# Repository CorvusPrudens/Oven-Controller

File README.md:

# Oven-Controller
 Hardware Firmware, and support software for an ATMEGA 328-P based reflow oven controller.

## Hardware

 The board is controlled by an ATMEGA328-P microcontroller running at 20 MHz. USB communication and flashing is handled with an FT232R USB to UART IC. The board uses a USB-C connector because every modern device should.
 <!--  -->

 The controller includes a MAX31865 PTD temperature sensor IC with headers for a three-wire PTD probe, a solid state relay, and two additional gpio. The board also include a 7-12 volt power input header and a standard Arduino ICSP header for bootloader flashing.

 The most prominent feature is, of course, the 128x64 pixel OLED display. The on-screen UI is navigated with the 6 pushbuttons arranged in a gamepad-like fashion.

 The board was designed in kiCad, but can be easily ported to Eagle.
<br /><br />
## Firmware

 The firmware provides an intuitive, menu-based UI for the user. Without any programming or reflashing, the user can define up to eight temperature profiles that persist even after power cycling. These profiles can then be called up to control a modified toaster oven via a solid state relay.

 The firmware provides out of the box support for a piezo buzzer on the available gpio terminal, which provides feedback for UI navigation and an open-door notification.
<br /><br /><br /><br /><br /><br /><br /><br /><br /><br />
## Software
 I have also written a few support programs with Processing and Python. They perform various functions, including generating timer settings for different clock frequencies, generating playable note sequences given a semi-intuitive note table entry, generating bitmaps from images (ideally monochromatic or dichromatic images), and a program that allows a connected computer to log and display the live temperature profile as recorded by the controller.

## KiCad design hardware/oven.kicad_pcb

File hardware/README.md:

# Hardware

<!--  -->

 This board combines several convenient features together to make an easy to use and highly capable reflow (toaster) oven controller. At the heart of the design is an ATMEGA328-P, with a few support features similar to what you might find on an Arduino board. This allows easy integration with the large Arduino ecosystem and convenient communication and flashing via USB (after flashing a bootloader via the ICSP header). To maximize performance, the 328-P is run at 5 volts -- supplied by either the USB Vbus or the included 7-12 volts LDO regulator. This allows the microcontroller to run at its highest rated frequency, 20 MHz, which is just enough to run all the UI screens at 30 frames per second.

 While the microcontroller can accept 5 volts, the two SPI connected modules -- the MAX31865 PTD probe sensor IC and the OLED display -- need 3.3 volts. Their power is supplied through another LDO, and the communication is routed through a very convenient level shifter, the TXB0108.

 The board itself is a 4 layer design. Of course, 4 layers is completely overkill for this design and would make no sense for a high-volume product. However, this is _not_ a high-volume product, and the manufacturer I use just so happened to drop their 4 layer prices insanely low. I'd be crazy not to make it 4!

 Finally, I'd like to highlight the use of USB-C. If I ever include USB functionality on a device, I will _always_ choose USB-C if I am able. Not only is it an aesthetically pleasing, reversible, fast, and powerful connection -- it's _dead easy_ to design with assuming you don't need its fancier features like power delivery or USB 3.0 (or the dreadfully named USB 3.1 gen 2!). All that's needed for a basic implementation is two resistors and a convenient USB 2.0 rated connector like the one I've used on this board. Give it a try!

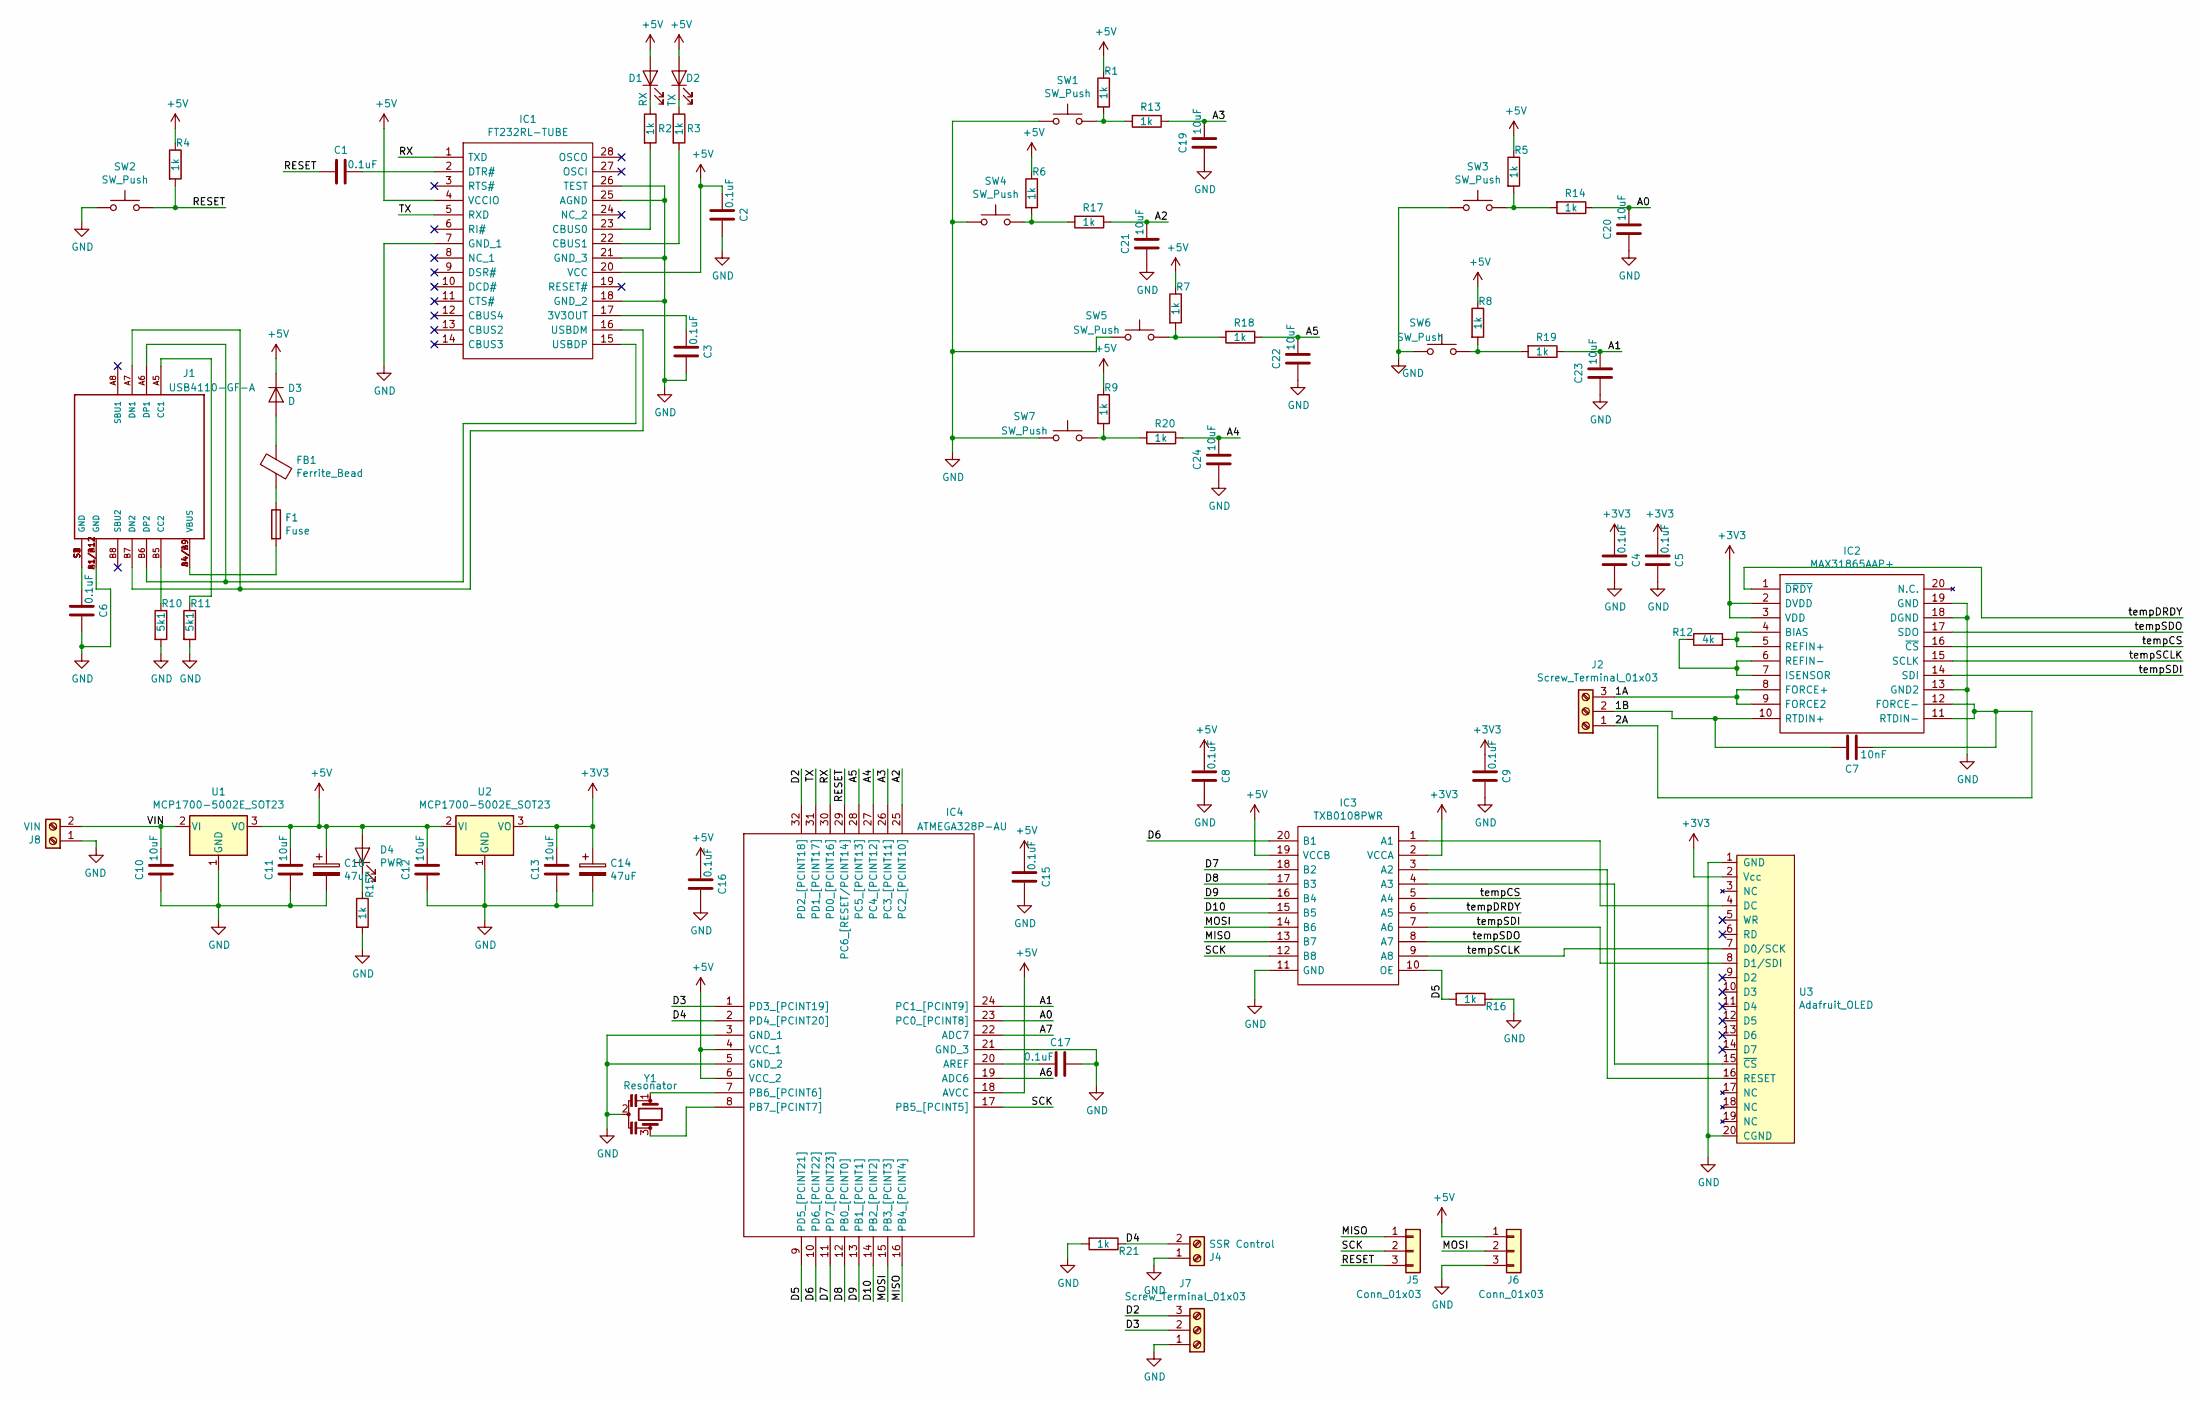
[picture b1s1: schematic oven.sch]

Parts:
C1, C2, C3, C4, C5, C6, C8, C9, C15, C16, C17: 0.1uF; C_0603_1608Metric_Pad1.05x0.95mm_HandSolder
C7: 10nF; C_0603_1608Metric_Pad1.05x0.95mm_HandSolder
C10, C11, C12, C13, C19, C20, C21, C22, C23, C24: 10uF; C_0805_2012Metric
C14, C18: 47uF; CP_EIA-3216-12_Kemet-S_Pad1.58x1.35mm_HandSolder
D1: RX; LED_0603_1608Metric_Pad1.05x0.95mm_HandSolder
D2: TX; LED_0603_1608Metric_Pad1.05x0.95mm_HandSolder
D3: D; DO-220AA
D4: PWR; LED_0603_1608Metric_Pad1.05x0.95mm_HandSolder
F1: Fuse; Fuse_0603_1608Metric_Pad1.05x0.95mm_HandSolder
FB1: Ferrite_Bead; L_0603_1608Metric_Pad1.05x0.95mm_HandSolder
IC1: FT232RL-TUBE; SOP65P780X200-28N; Mouser Part Number 895-FT232RL-TUBE
IC2: MAX31865AAP+; SOP65P778X199-20N; Mouser Part Number 700-MAX31865AAP+
IC3: TXB0108PWR; SOP65P640X120-20N; Mouser Part Number 595-TXB0108PWR
IC4: ATMEGA328P-AU; QFP80P900X900X120-32N; Mouser Part Number 556-ATMEGA328P-AU
J1: USB4110-GF-A; GCT_USB4110-GF-A
J2, J7: Screw_Terminal_01x03; TerminalBlock_4Ucon_1x03_P3.50mm_Horizontal
J4: SSR Control; TerminalBlock_4Ucon_1x02_P3.50mm_Horizontal
J5, J6: Conn_01x03; PinHeader_1x03_P2.54mm_Vertical
J8: VIN; TerminalBlock_4Ucon_1x02_P3.50mm_Horizontal
R1, R2, R3, R4, R5, R6, R7, R8, R9, R13, R14, R15, R16, R17, R18, R19, R20, R21: 1k; R_0603_1608Metric_Pad1.05x0.95mm_HandSolder
R10, R11: 5k1; R_0603_1608Metric_Pad1.05x0.95mm_HandSolder
R12: 4k; R_0603_1608Metric_Pad1.05x0.95mm_HandSolder
SW1, SW2, SW3, SW4, SW5, SW6, SW7: SW_Push; SW_PUSH_6mm_H4.3mm
U1, U2: MCP1700-5002E_SOT23; SOT-89-3
U3: Adafruit_OLED
Y1: Resonator; CSTNE16M0V530000R0

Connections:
+3V3: C4.2, C5.2, C9.2, C13.1, C14.1, IC2.2 (DVDD), IC2.3 (VDD), IC3.2 (VCCA), U2.3 (VO), U3.2 (Vcc)
+5V: C2.2, C8.2, C11.1, C12.1, C15.2, C16.2, C18.1, D1.2 (A), D2.2 (A), D3.1 (K), D4.2 (A), IC1.4 (VCCIO), IC1.20 (VCC), IC3.19 (VCCB), IC4.4 (VCC_1), IC4.6 (VCC_2), IC4.18 (AVCC), J6.1, R1.1, R4.1, R5.1, R6.1, R7.1, R8.1, R9.1, U1.3 (VO), U2.2 (VI)
/1A: IC2.8 (FORCE+), IC2.9 (FORCE2), J2.3
/1B: C7.1, IC2.10 (RTDIN+), J2.2
/2A: C7.2, IC2.11 (RTDIN-), IC2.12 (FORCE-), J2.1
/A0: C20.1, IC4.23 (PC0_[PCINT8]), R14.1
/A1: C23.1, IC4.24 (PC1_[PCINT9]), R19.1
/A2: C21.1, IC4.25 (PC2_[PCINT10]), R17.1
/A3: C19.1, IC4.26 (PC3_[PCINT11]), R13.1
/A4: C24.1, IC4.27 (PC4_[PCINT12]), R20.1
/A5: C22.1, IC4.28 (PC5_[PCINT13]), R18.1
/A6: IC4.19 (ADC6)
/A7: IC4.22 (ADC7)
/D2: IC4.32 (PD2_[PCINT18]), J7.3
/D3: IC4.1 (PD3_[PCINT19]), J7.2
/D4: IC4.2 (PD4_[PCINT20]), J4.2, R21.1
/D5: IC3.10 (OE), IC4.9 (PD5_[PCINT21]), R16.2
/D6: IC3.20 (B1), IC4.10 (PD6_[PCINT22])
/D7: IC3.18 (B2), IC4.11 (PD7_[PCINT23])
/D8: IC3.17 (B3), IC4.12 (PB0_[PCINT0])
/D9: IC3.16 (B4), IC4.13 (PB1_[PCINT1])
/D10: IC3.15 (B5), IC4.14 (PB2_[PCINT2])
/MISO: IC3.13 (B7), IC4.16 (PB4_[PCINT4]), J5.1
/MOSI: IC3.14 (B6), IC4.15 (PB3_[PCINT3]), J6.2
/RESET: C1.2, IC4.29 (PC6_[RESET/PCINT14]), J5.3, R4.2, SW2.2
/RX: IC1.1 (TXD), IC4.30 (PD0_[PCINT16])
/SCK: IC3.12 (B8), IC4.17 (PB5_[PCINT5]), J5.2
/TX: IC1.5 (RXD), IC4.31 (PD1_[PCINT17])
/VIN: C10.1, J8.2, U1.2 (VI)
/tempCS: IC2.16 (~CS), IC3.5 (A4)
/tempDRDY: IC2.1 (~DRDY), IC3.6 (A5)
/tempSCLK: IC2.15 (SCLK), IC3.9 (A8), U3.7 (D0/SCK)
/tempSDI: IC2.14 (SDI), IC3.7 (A6), U3.8 (D1/SDI)
/tempSDO: IC2.17 (SDO), IC3.8 (A7)
GND: C2.1, C3.1, C4.1, C5.1, C6.1, C8.1, C9.1, C10.2, C11.2, C12.2, C13.2, C14.2, C15.1, C16.1, C17.1, C18.2, C19.2, C20.2, C21.2, C22.2, C23.2, C24.2, IC1.7 (GND_1), IC1.18 (GND_2), IC1.21 (GND_3), IC1.25 (AGND), IC1.26 (TEST), IC2.13 (GND2), IC2.18 (DGND), IC2.19 (GND), IC3.11 (GND), IC4.3 (GND_1), IC4.5 (GND_2), IC4.21 (GND_3), J1.A1/B12 (GND), J1.B1/A12 (GND), J4.1, J6.3, J7.1, J8.1, R10.2, R11.2, R15.2, R16.1, R21.2, SW1.1, SW2.1, SW3.1, SW4.1, SW5.1, SW6.1, SW7.1, U1.1 (GND), U2.1 (GND), U3.1 (GND), U3.20 (CGND), Y1.2
unnamed: C1.1, IC1.2 (DTR#)
unnamed: C3.2, IC1.17 (3V3OUT)
unnamed: C6.2, J1.S1 (GND), J1.S2 (GND), J1.S3 (GND), J1.S4 (GND)
unnamed: C17.2, IC4.20 (AREF)
unnamed: D1.1 (K), R2.1
unnamed: D2.1 (K), R3.1
unnamed: D3.2 (A), FB1.1
unnamed: D4.1 (K), R15.1
unnamed: F1.1, FB1.2
unnamed: F1.2, J1.A4/B9 (VBUS), J1.B4/A9 (VBUS)
unnamed: IC1.15 (USBDP), J1.A6 (DP1), J1.B6 (DP2)
unnamed: IC1.16 (USBDM), J1.A7 (DN1), J1.B7 (DN2)
unnamed: IC1.22 (CBUS1), R3.2
unnamed: IC1.23 (CBUS0), R2.2
unnamed: IC2.4 (BIAS), IC2.5 (REFIN+), R12.2
unnamed: IC2.6 (REFIN-), IC2.7 (ISENSOR), R12.1
unnamed: IC3.1 (A1), U3.4 (DC)
unnamed: IC3.3 (A2), U3.16 (RESET)
unnamed: IC3.4 (A3), U3.15 (~CS)
unnamed: IC4.7 (PB6_[PCINT6]), Y1.1
unnamed: IC4.8 (PB7_[PCINT7]), Y1.3
unnamed: J1.A5 (CC1), R11.1
unnamed: J1.B5 (CC2), R10.1
unnamed: R1.2, R13.2, SW1.2
unnamed: R5.2, R14.2, SW3.2
unnamed: R6.2, R17.2, SW4.2
unnamed: R7.2, R18.2, SW5.2
unnamed: R8.2, R19.2, SW6.2
unnamed: R9.2, R20.2, SW7.2

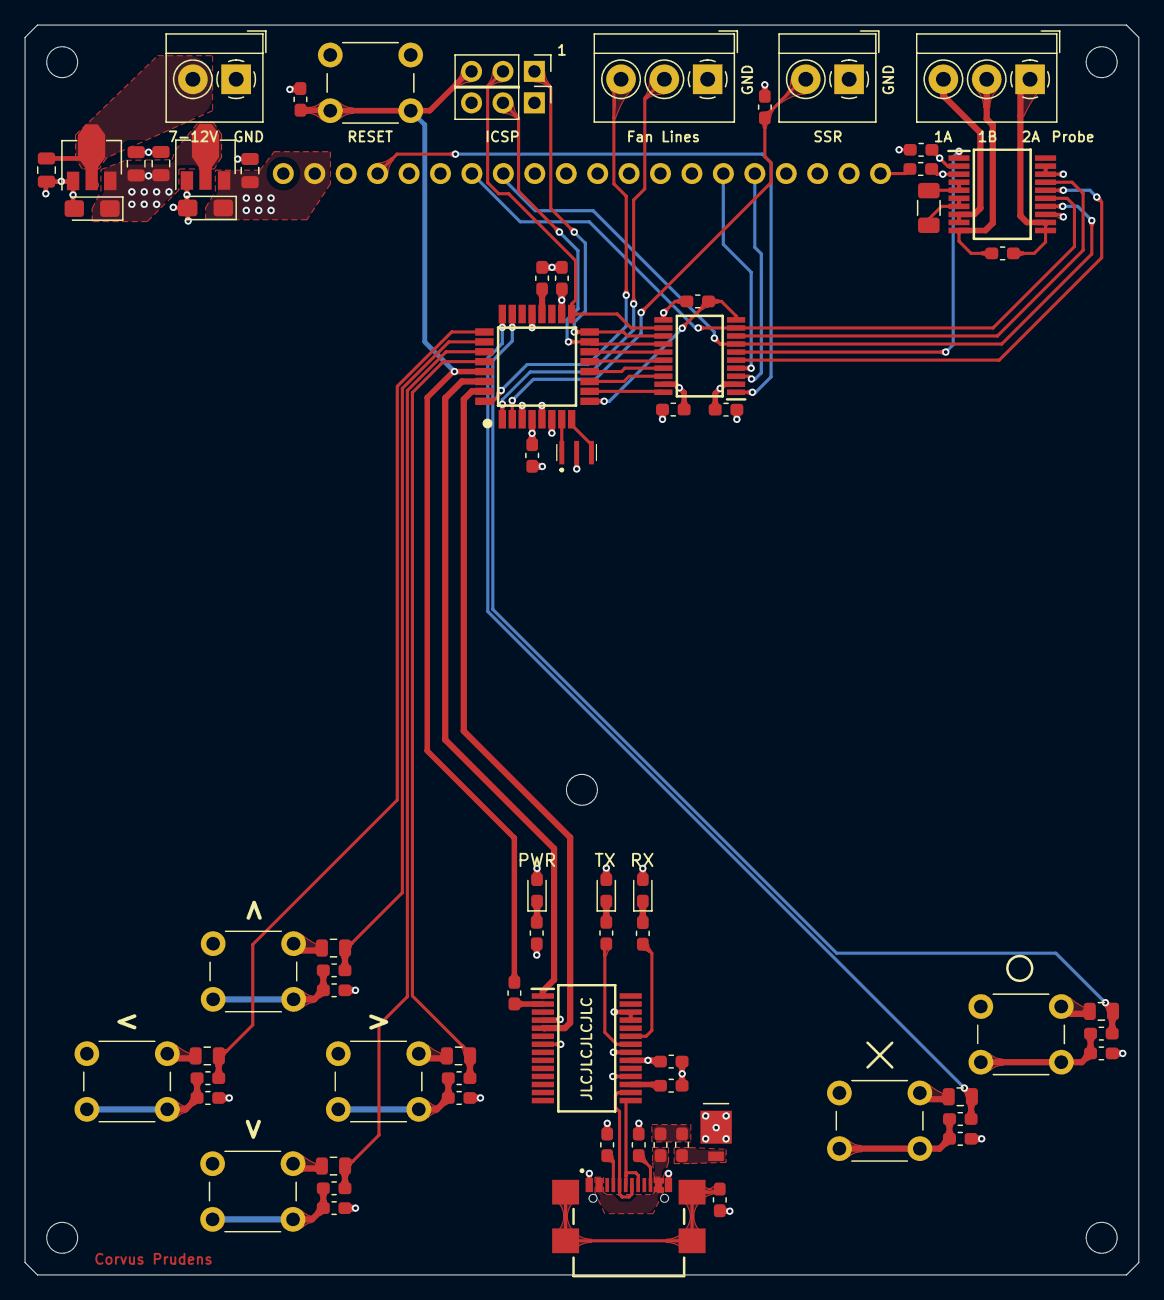
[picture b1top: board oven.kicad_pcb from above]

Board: 4 copper layers, 90.0 x 101.0 mm, 73 parts (0 on the bottom side), 62 nets.

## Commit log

2020-09-12 Adding Libraries in with code
2020-09-12 Included entire libraries
2020-09-12 Updated Structure
2020-09-12 Consolidated library code
2020-09-12 cleanup
2020-09-12 Added bitmap generator
2020-09-12 Adding Images
2020-09-12 img mor smol
2020-09-12 included software
2020-09-12 image formatting
2020-09-12 more formatting
2020-09-12 even more formatting
2020-09-12 Update README.md
    mfw github is my only markdown formatter
2021-02-08 small additions to utils
